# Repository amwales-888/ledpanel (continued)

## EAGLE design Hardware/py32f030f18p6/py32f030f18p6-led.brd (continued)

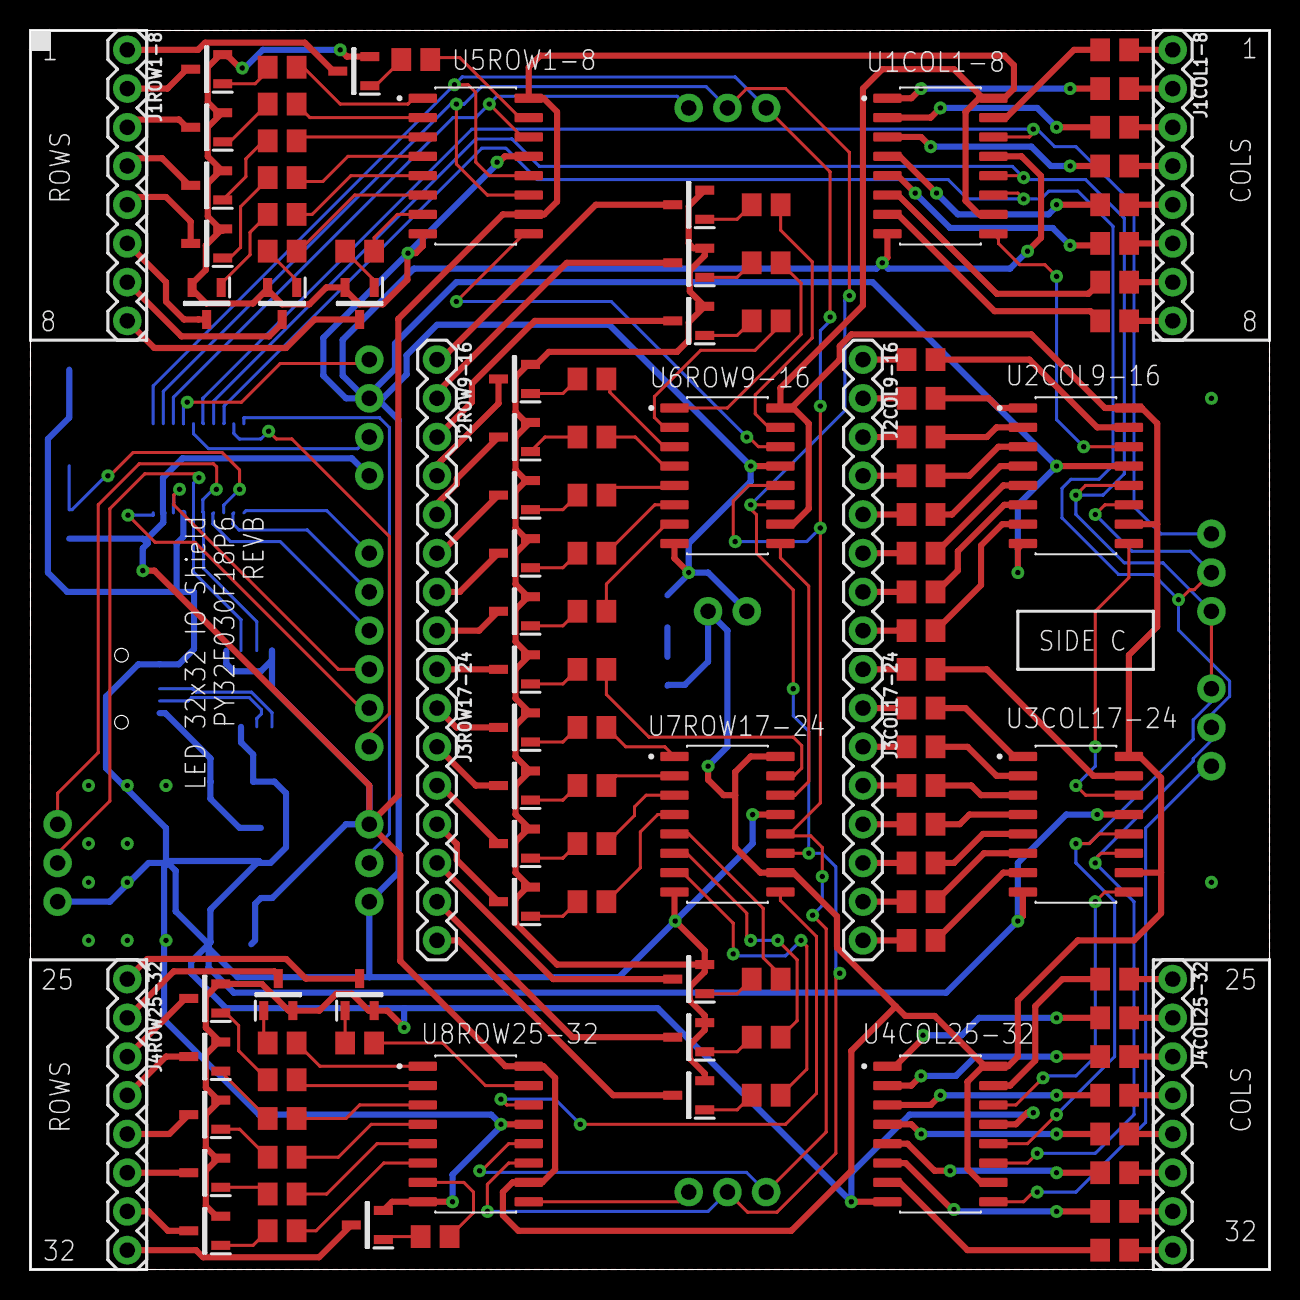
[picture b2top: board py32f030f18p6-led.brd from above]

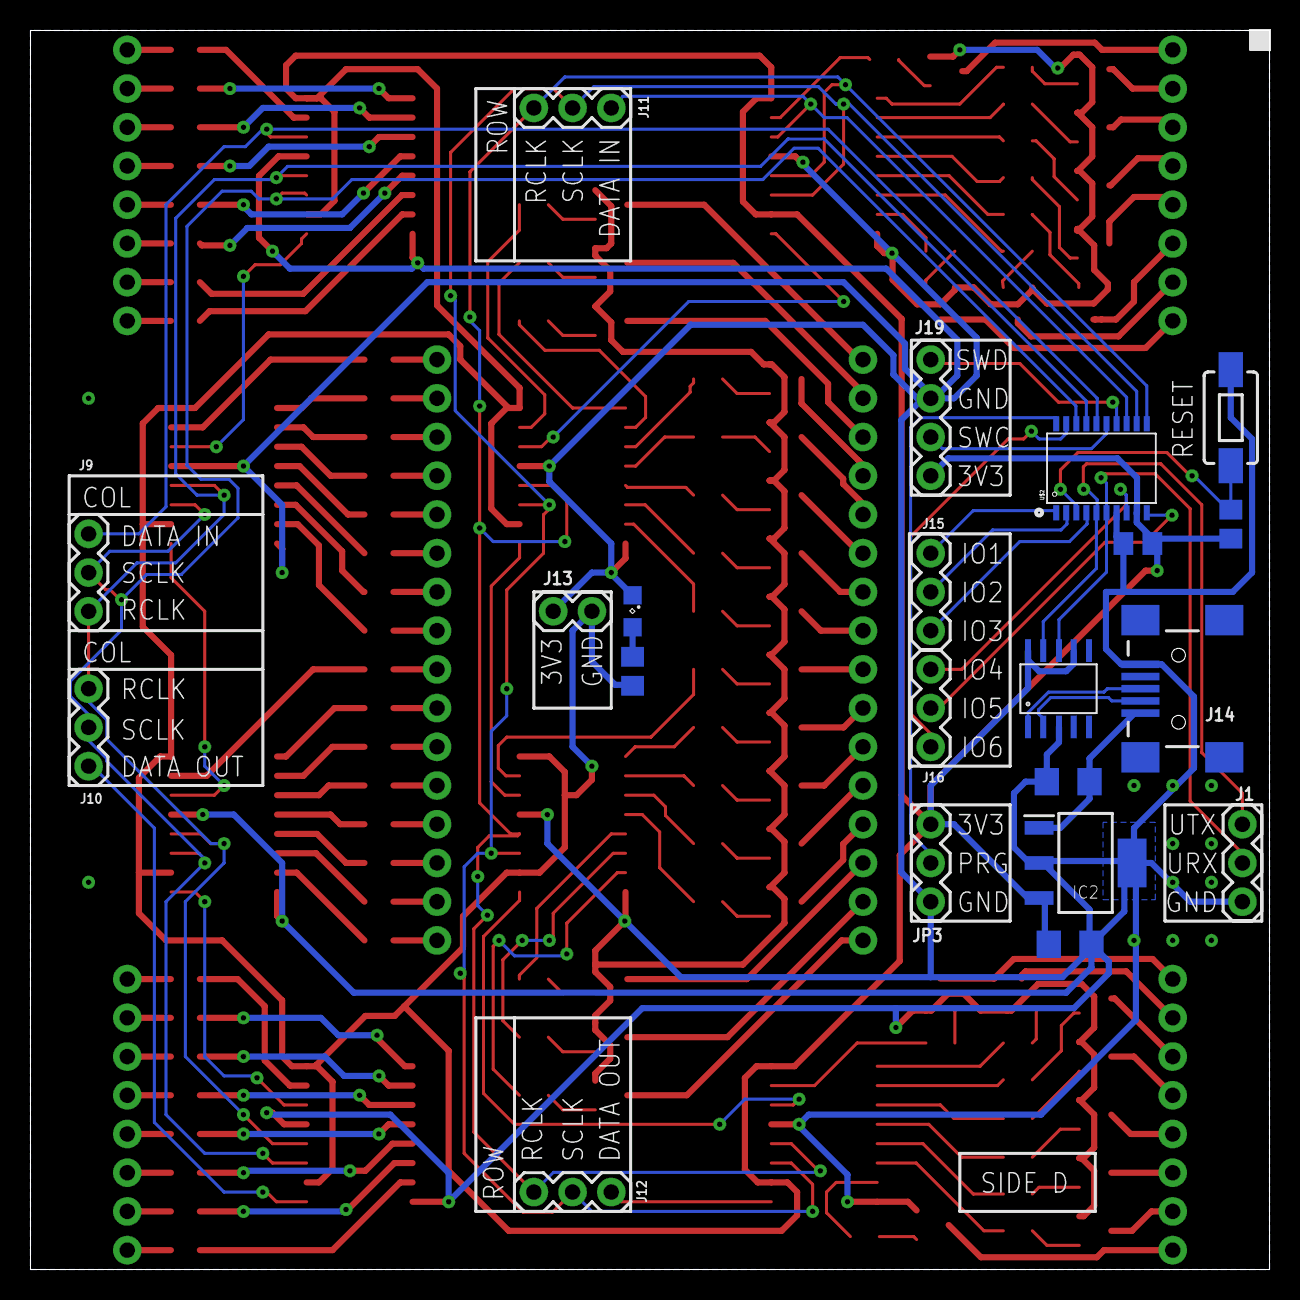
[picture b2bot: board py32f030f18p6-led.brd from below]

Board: 2 copper layers, 81.3 x 81.3 mm, 133 parts (21 on the bottom side), 192 nets.

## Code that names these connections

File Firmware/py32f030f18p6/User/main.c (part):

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
		SR1

		PA11 - ROW_DATA_IN  Data    14
		PA10 - ROW_SCLK_IN  Clock   11
		PA9  - ROW_RCLK_IN  Latch   12

		SR2

		PB4  - COL_DATA_IN	Data
		PB6  - COL_SCLK_IN	Clock
		PB5  - COL_RCLK_IN	Latch

*/

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    
static void outputBitmapX(uint8_t *ptr) {

	LL_GPIO_TogglePin(GPIOA, LL_GPIO_PIN_8);					// GPIO5

	for (int row=0; row<MAX_ROW; row++) {
		
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  LL_GPIO_SetPinMode(GPIOA, LL_GPIO_PIN_11, LL_GPIO_MODE_OUTPUT);


  LL_GPIO_SetPinMode(GPIOA, LL_GPIO_PIN_8, LL_GPIO_MODE_OUTPUT);	// GPIO5


	
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
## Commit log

2024-10-24 Adding hardware and firmware
    firmware is just a skeleton for now
2024-11-07 Got row/col reversed
2024-11-10 Added rx/tx breakout
2024-11-11 Final checks ( removed dimensions ) regenerate gerbers to submit to jlpcb
2024-11-11 cropped and scaled images
2024-11-28 MCU running at 48Mhz ( 24Mhz Internal * 2 PLL )
    Display appears flicker free and leds same brightness, simple test running displaying dots. Need to investigate divider on one of the busses, I think I need a few cycles delay between toggling the sh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
2024-11-30 Chip now running at 48Mhz
2024-12-09 Refresh 32x32 at 1ms, 4 planes at 4ms, so 250Hz refresh.
    Refresh 32x32 at 1ms, 4 planes at 4ms, so 250Hz refresh. Planes represent brightness, same bit across 4 planes will light LED brightest, single bit on 1 plane will light LED dimmest. Using nordic pow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
2024-12-17 added a simple scrolling message
